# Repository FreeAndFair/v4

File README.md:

dkvs
====

**The DemTech Kiosk Voting System.**

*The DemTech Project*

Editor: Joseph Kiniry

Contributors: Attila Sukosd, Steffen Dalsgaard

Abstract
--------

The DemTech Kiosk Voting System (DKVS henceforth) is a hardware and
software system for use in supervised elections.  The DKVS is meant to
be a low-cost, mission-critical system that reliably records voter
intent, produces a well-formed digital and paper ballot pair that
captures a voter's intent, securely logs all actions taken by the
hardware and software, and reports on the election and counts all
recorded ballots at the end of an election.  The design and
development of DKVS is conducted according to mission- and
safety-critical standards, thus treating democracy and elections as a
safety- & mission-critical system.  This system may be used as the
foundation for further experimentation in supervised voting systems,
incorporating our research work in logic-based elections,
zero-knowledge proofs, certificates, and more at some future date.

Discussion
----------

To participate in an election in Denmark today, a voter:

1. goes to their assigned polling place,
2. identifies him/herself using a voter card that was mailed to them in the preceding weeks,
3. is handed a paper ballot,
4. goes into a private polling booth,
5. uses a pencil to mark the ballot in a single location to indicate their vote,
6. folds the completed ballot to hide their mark,
7. exits the polling booth,
8. puts their completed ballot into an opaque, sealed ballot box,
9. exits the polling place.

> Steffen: Perhaps add a brief para on the practice of postal voting. Have you considered how postal votes could be integrated in the DKVS?

A ballot in Denmark is a sheet of white or yellow paper printed with
black ink that is at least A3 sized in recent years.  The longest
ballots on record are approximately one meter long.  On it, in a
random order, is a list of every political party certified for the
election, and under every party entry is a list of every certified
candidate from that party.  The ordering of candidates is determined
by their party.

To complete a well-formed "unspoiled" ballot a voter must put a clear
mark next to either the party for which they are voting or next to a
specific candidate for which they are voting.  There are complex rules
about what constitutes an "unspoiled" ballot, particularly in the
presence of multiple consistent and inconsistent markings, smudges,
location of marks, different kinds of marks, etc.

In each election there are several thousand ballots nationwide that
are deemed "spoiled" as they violate these well-formedness guidelines.

At the end of an election, in the presence of witnesses, the ballot
boxes are emptied and the ballots that they contained are manually
collated according to the political party chosen on each ballot.  Then
each pile of ballots is counted by hand by two or more volunteers.
Ballot stacks are counted at least twice to obtain a per-party tally,
known as the "rough count", which is reported to the central electoral
officer by telephone and computer system.

Ballots are then securely bundled following a specific published
procedure and are transported by volunteers in taxis to a central
location.  The bundles are stored in a secure storage facility and
guarded by the police.  All of this happens in a single evening.

The next day, all securely bundled ballots are unpacked in the
presence of witnesses.  Each per-municipality bundle of ballots is
unpacked onto a single table.  At each table, municipality workers
perform another partitioning on the per-party ballot stacks, collating
them according to the individual candidate that received a vote on
each ballot in question.  Thus, if there are K candidates for party P,
party P has at most K+1 stacks of ballots after collation.  The
"extra" stack is for those votes that are assigned to the party,
rather than to a specific individual.

Each per-candidate stack, as well as the candidate-less stack, is then
concurrently counted by hand by two or more municipality workers. Each
stack is counted at least two times and there is a published mechanism
by which a count is deemed "correct enough" that related to the
difference between a tally in any two sequential counts.  This is
knows as the "fine count".

Intermediate results and per-candidate and per-party counting results
are reported to a central table by writing on little slips of paper
and carrying them across the room.  Intermediate results are submitted
to a central authority via a networked computer system and via
telephone and are published to the public via a web site.

Once all tallies at all tables complete their tallying, the election
fine count is deemed complete.

There are several recognized problems with the existing electoral
system in Denmark that are mentioned in the recent proposed change in
law.

> Steffen: Perhaps mention that the intent here is not to discuss the severity of these problems compared to the overall trust etc. in the present system, but to suggest a way in which they can be minimized?

* Many of the disabled do not have the ability to independently vote
  as they require, by law, the help of two electoral assistants to
  complete their ballot.  The participation of assistants violates the
  voter's right to private ballot, and may violate their right to a
  uncoerced ballot.

* Manually counting votes is slow and error-prone, particularly when
  those counting are working long hours in a poor
  environment. Published error rates for manually counting voters
  range from 0.1% to 1%, depending upon the complexity of the ballots,
  the state of those counting, specifics of the counting process, and
  the speed at which they count.

There are some other problems observed by election observers, both
DemTech personnel and others:

* The participation of municipality workers and the lack of
  independent observers at the fine count opens up many opportunities
  or insider attack and fraud.

* The participation of municipality workers in the fine count
  increases the cost of an election significantly.

* The computers and networks used to record and report tallies on both
  election day and during the fine count are not robust, insecure,
  opaque, proprietary software systems and use ad hoc protocols (both
  human and technical).

DemTech has already made a small number of simple recommendations to
the Head of Elections with an aim toward improving the correctness,
improving the security, and lowering the cost of the existing
electoral system with the introduction of no IT technology [citation].

DemTech has also submitted a formal response to the proposed changes
in electoral law to permit trials in evoting [citation].  This system
is meant to fulfill all of the suggested recommendations put forth in
that response (e.g., conformance to various ISO standards for software
quality and security).

The DemTech project, by virtue of its original grant proposal,
promised to experiment with non-binding digital elections during
national elections in Denmark in 2013 and beyond.  Thus, developing
open technology like this project is directly within our plan and
mandate.

Now that the Ministry responsible for elections has proposed a change
in electoral law in order to experiment with digital technologies in
the recording of voter intent, the DemTech research project has an
even stronger incentive to develop new technology fit for this
purpose.  Moreover, if we develop open source, unencumbered technology
that fulfills the requirements set forth by law, then municipalities
can decide to use our technology in their own binding trials if they
wish.

Requirements
------------

The requirements we impose on the design and development of this
system come directly from, or are directly derived from, existing
national and international laws, guidelines, and recognized best
practices in elections (digital or traditional).

There are also a number of technical requirements that we stipulate
that derive from best practices in rigorous software engineering and
information security.

All standards, laws, guidelines and the like mentioned herein are
cited at the end of this document.

Mandatory Requirements
----------------------

TBD by Joe and Attila

Optional Requirements
---------------------

TBD by Joe and Attila

Goals
-----

This system is designed and developed to:

* be one of the systems demonstrated to the Danish government in 2013,
* be one of the systems demonstrated and evaluated by Danish voters in the 2013 elections,
* be exhibited to the world as the best evoting system ever produced,
* be used as a model for best-in-industry systems development in election equipment,
* be a case-study in our early ideas in the Trust-by-Design methodology,
* and fulfill the evaluation requirements injected by DemTech members, partners, the government, and the electorate.

Open Questions
--------------

* stateful vs. stateless kiosk
* voter identification to machine via token
* digital vote storage
* digital vote encoding and encryption
* should digital technology be used to sort ballots

Project Planning
----------------

TBD by Joe and Attila, including summary of timeline and milestones

Gantt chart, milestones, tasks, responsibilities, all with
cross-references to public tracking of project in Trac will be in the
DKVS Planning document, mentioned below

Other Related Documents
-----------------------

To best understand the design and development of this system, please
refer to the following documents.  We suggest reading them in the
stipulated order.  Note that each of these documents is short,
focused, and to-the-point.  We do not avoid formalism when required.
Recall that DKVS means “DemTech Kiosk Voting System”.

* DKVS Project Planning
* DKVS Process
* DKVS Methodology
* The Trust-by-Design Methodology
* DKVS Domain Analysis
* DKVS Formal Requirements
* DKVS Risk Analysis
* DKVS Hardware Foundation
* DKVS Software Foundation
* DKVS Architecture
* DKVS Formal Design
* DKVS Cryptography
* DKVS Implementation
* DKVS Security
* DKVS Validation
* DKVS Verification
* DKVS Traceability

References
----------

* Folketingsvalget den 15. september 2011. (2011).

* Recommendations to the Danish Government to Improve the Accuracy,
  Secrecy, and Cost of Modern Danish Elections (ed. Joseph Kiniry)

* DemTech. Consultation response during the public hearing on the
  proposal to change the Danish election laws on elections for the
  Danish Parliament, of Danish members to the European Parliament, and
  for municipalities and regions (in order to experiment with digital
  voting and tallying). January, 2013.

* Council of Europe. (2004a). Reflections on the future of democracy in Europe.

* Council of Europe. (2004b). Legal, operational and technical
  standards for e-voting (Rec(2004)11).

* Council of Europe. (2010). E-voting handbook - key steps in the
  implementation of e-enabled elections.

* Council of Europe. (2011). Guidelines on transparency of e-enabled
  elections (GGIS (2010) 5 fin. E).

* European Parliament. (2008). E-public, e-participation and e-voting
  in Europe - prospects and challenges.

* Federal Election Commission. (2002). Voting Systems Performance and
  Test Standards : An Overview (Vol. I).

* IEEE Computer Society. (2012). IEEE Standard for Electronic
  Distribution of Blank Ballots for Voting Systems (IEEE Std 1622).

* Jones, D. W., & Simons, B. (2012). Broken Ballots. University
  of Chicago Press. Retrieved from
  http://www.amazon.co.uk/Broken-Ballots-Center-Language-Information/dp/1575866366

* Harris, B. (2004). Black Box Voting - Ballot Tampering in the 21st
  Century. Retrieved from http://amerivote.com/ibip/docs/bbv_Part1.pdf

* Herrnson, P. S., Niemi, R. G., Hanmer, M. J., Bederson, B. B.,
  Conrad, F. G., & Traugott, M. W. (2008). Voting Technology: The
  Not-so-simple Act of Casting a Ballot. Brookings Institution
  Press. Retrieved from
  http://www.amazon.co.uk/Voting-Technology-Not-so-simple-Casting-Ballot/dp/0815735634

* Rubin, A. D. (2006). Brave New Ballot: The Battle to Safeguard
  Democracy in the Age of Electronic Voting. Morgan Road
  Books. Retrieved from
  http://www.amazon.co.uk/Brave-New-Ballot-Safeguard-Electronic/dp/0767922107

* Shamos, M. I. (2011). Electronic Voting Glossary.

* Goldsmith, B. (2011). Electronic Voting & Counting Technologies.

Appendices
----------

Domain Dictionary
-----------------

Risk Analysis
-------------

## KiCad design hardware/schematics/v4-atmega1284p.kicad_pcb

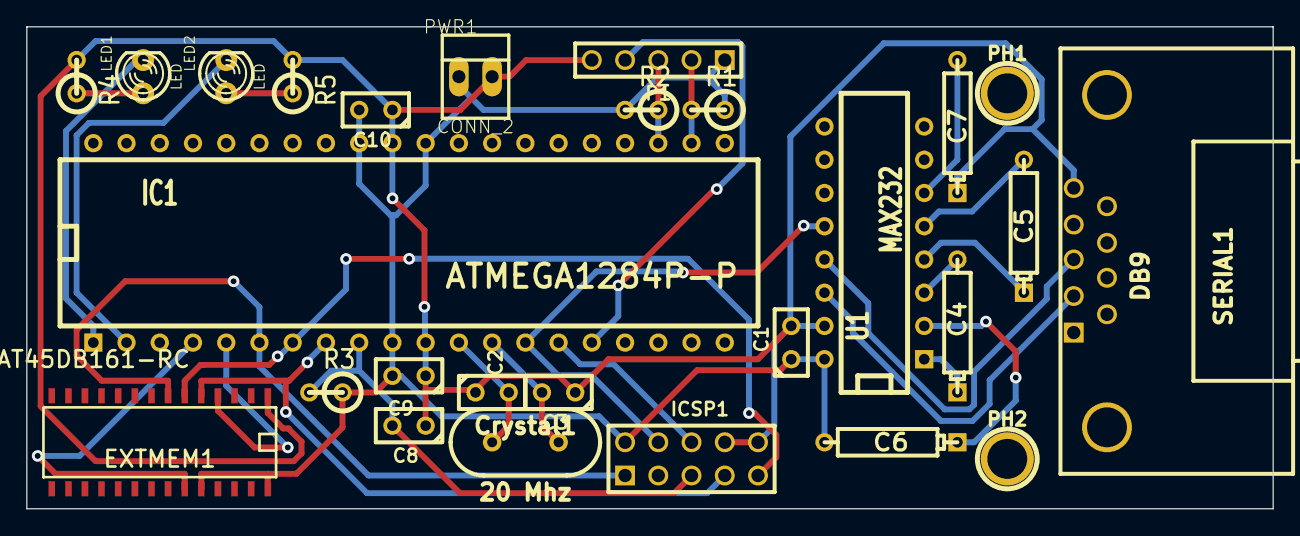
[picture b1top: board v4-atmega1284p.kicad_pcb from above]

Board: 2 copper layers, 95.2 x 36.8 mm, 27 parts (0 on the bottom side), 27 nets.

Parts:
C1: 22 uF; C1
C2, C3: 22 pF; C1
C4, C5, C6, C7: 1 uF; CP4
C8, C9, C10: 100nF; C1
Crystal1: 20 Mhz; HC-49V
EXTMEM1: AT45DB161-RC; S0IC28N
IC1: ATMEGA1284P-P; DIP-40__600
ICSP1: CONN_5X2; PIN_ARRAY_5x2
LED1, LED2: LED; LED-3MM
P1: CONN_5; PIN_ARRAY_5x1
PH1, PH2: P***; 1pin
PWR1: CONN_2; PINHEAD1-2
R1, R2: 4.7 kOhm; R1
R3: 100 kOhm; R1
R4, R5: 1 kOhm; R1
SERIAL1: DB9; DB9MC
U1: MAX232; DIP-16__300

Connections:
+3.3V: C1.1, C6.2, C9.2, C10.2, EXTMEM1.24, EXTMEM1.28, IC1.10, IC1.30, IC1.32, ICSP1.2, P1.1, PWR1.1, R1.1, R2.2, R3.1, U1.16
GND: C1.2, C2.1, C3.1, C7.1, C8.1, C9.1, C10.1, EXTMEM1.1, IC1.11, IC1.31, ICSP1.8, ICSP1.10, P1.5, PWR1.2, R4.2, R5.2, SERIAL1.5, U1.15
unnamed: LED2.1, R5.1
unnamed: IC1.1, LED1.2
unnamed: EXTMEM1.4, IC1.5
unnamed: IC1.15, ICSP1.6
unnamed: IC1.14, ICSP1.4, U1.12
unnamed: LED1.1, R4.1
unnamed: IC1.22, P1.2, R1.2
unnamed: IC1.2, LED2.2
unnamed: EXTMEM1.6, IC1.7, ICSP1.9
unnamed: EXTMEM1.5, IC1.8, ICSP1.7
unnamed: C8.2, IC1.9, ICSP1.5, R3.2
unnamed: C7.2, U1.6
unnamed: C6.1, U1.2
unnamed: SERIAL1.3, U1.13
unnamed: SERIAL1.2, U1.14
unnamed: EXTMEM1.23, IC1.4
unnamed: EXTMEM1.7, IC1.6, ICSP1.1
unnamed: IC1.16, P1.4
unnamed: IC1.23, P1.3, R2.1
unnamed: C3.2, Crystal1.2, IC1.13
unnamed: C2.2, Crystal1.1, IC1.12
unnamed: C4.1, U1.1
unnamed: C4.2, U1.3
unnamed: C5.2, U1.5
unnamed: C5.1, U1.4

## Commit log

2013-02-20 Moved body in from Google document.
2013-02-22 Initial project description for the hardware
2013-02-22 Updated file extension
2013-02-22 Updated formatting in the project description
2013-02-22 Initial project description for the JVM
2013-03-05 Initial writeup on possible MCUs on the market
2013-03-05 Formatting fixes
2013-03-18 More docs
2013-05-17 Import of electronics schematics
2013-05-17 3D CAD import
2013-05-17 AVR NaCL import
2013-08-01 Typos reported by Ian Qvist.
2013-11-30 Added V4 UART image
2013-11-30 New pictures for the v4 hardware
2013-11-30 Added a very simple v4 hardware component overview
2013-11-30 V4 3d case concept + images
2013-11-30 Added resized 3d case concept image
2013-12-01 V4 i2c images
2013-12-01 Corrected units in the 3D cad file
2013-12-01 Draft report
2017-05-16 Create LICENSE
2017-05-16 Update LICENSE
